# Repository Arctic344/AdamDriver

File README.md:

# AdamDriver, the PCA9685 based MotorDriver
I created a compact quad-motor driver for a project

It uses a PCA9685 PWM controller and two TB6612FNG chips to run up to 4 motors from 4.5V to 13.5V

It is functionally the same as [this arduino shield](https://learn.adafruit.com/adafruit-motor-shield-v2-for-arduino/overview), but without the servo drivers and such.

I dont know what I am doing, so please do not attempt to use this driver.

If for some reason you have a question about this stuff, add me @arctic344 on discord.

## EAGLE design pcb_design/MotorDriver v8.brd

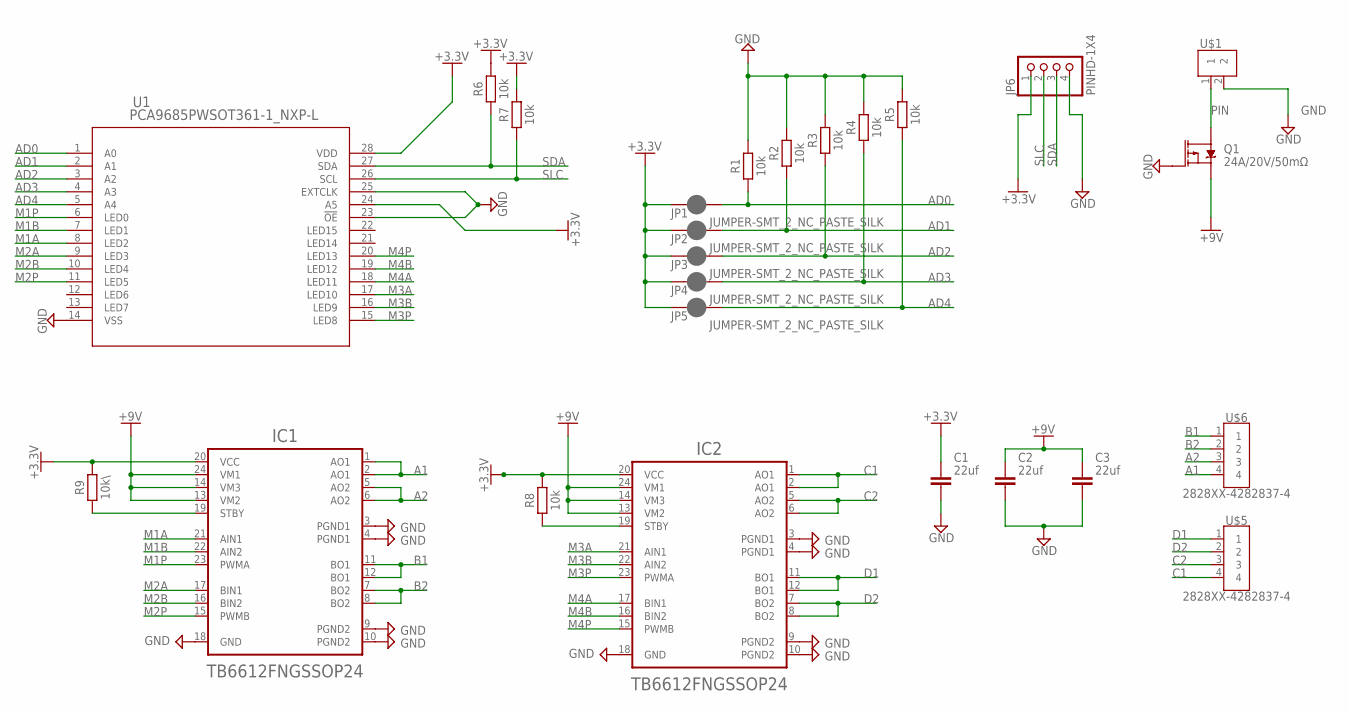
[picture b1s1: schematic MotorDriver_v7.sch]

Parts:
C1, C2, C3: 22uf; CAPC2012X110
IC1, IC2: TB6612FNGSSOP24; SOP65P760X160-24N
JP1, JP2, JP3, JP4, JP5: JUMPER-SMT_2_NC_PASTE_SILK; SMT-JUMPER_2_NC_PASTE_SILK
JP6: PINHD-1X4; 1X04
Q1: 24A/20V/50mΩ; TO220V
R1, R2, R3, R4, R5, R6, R7, R8: 10k; RESC1005X40
R9: 10k\; RESC1005X40
U1: PCA9685PWSOT361-1_NXP-L; SOT361-1_NXP-L
U$1: 2828XX-2282834-2; TERMBLK_254-2N
U$5, U$6: 2828XX-4282837-4; TERMBLK_508-4N

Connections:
+3.3V: C1.1, IC1.20 (VCC), IC2.20 (VCC), JP1.1, JP2.1, JP3.1, JP4.1, JP5.1, JP6.1, R6.2, R7.2, R8.2, R9.2, U1.24 (A5), U1.28 (VDD)
+9V: C2.1, C3.1, IC1.13 (VM2), IC1.14 (VM3), IC1.24 (VM1), IC2.13 (VM2), IC2.14 (VM3), IC2.24 (VM1), Q1.3 (S)
A1: IC1.1 (AO1), IC1.2 (AO1), U$6.4
A2: IC1.5 (AO2), IC1.6 (AO2), U$6.3
AD0: JP1.2, R1.1, U1.1 (A0)
AD1: JP2.2, R2.1, U1.2 (A1)
AD2: JP3.2, R3.1, U1.3 (A2)
AD3: JP4.2, R4.1, U1.4 (A3)
AD4: JP5.2, R5.1, U1.5 (A4)
B1: IC1.11 (BO1), IC1.12 (BO1), U$6.1
B2: IC1.7 (BO2), IC1.8 (BO2), U$6.2
C1: IC2.1 (AO1), IC2.2 (AO1), U$5.4
C2: IC2.5 (AO2), IC2.6 (AO2), U$5.3
D1: IC2.11 (BO1), IC2.12 (BO1), U$5.1
D2: IC2.7 (BO2), IC2.8 (BO2), U$5.2
GND: C1.2, C2.2, C3.2, IC1.3 (PGND1), IC1.4 (PGND1), IC1.9 (PGND2), IC1.10 (PGND2), IC1.18 (GND), IC2.3 (PGND1), IC2.4 (PGND1), IC2.9 (PGND2), IC2.10 (PGND2), IC2.18 (GND), JP6.4, Q1.1 (G), R1.2, R2.2, R3.2, R4.2, R5.2, U1.14 (VSS), U1.23 (!OE), U1.25 (EXTCLK), U$1.2
M1A: IC1.21 (AIN1), U1.8 (LED2)
M1B: IC1.22 (AIN2), U1.7 (LED1)
M1P: IC1.23 (PWMA), U1.6 (LED0)
M2A: IC1.17 (BIN1), U1.9 (LED3)
M2B: IC1.16 (BIN2), U1.10 (LED4)
M2P: IC1.15 (PWMB), U1.11 (LED5)
M3A: IC2.21 (AIN1), U1.17 (LED10)
M3B: IC2.22 (AIN2), U1.16 (LED9)
M3P: IC2.23 (PWMA), U1.15 (LED8)
M4A: IC2.17 (BIN1), U1.18 (LED11)
M4B: IC2.16 (BIN2), U1.19 (LED12)
M4P: IC2.15 (PWMB), U1.20 (LED13)
unnamed: IC2.19 (STBY), R8.1
unnamed: IC1.19 (STBY), R9.1
PIN: Q1.2 (D), U$1.1
SDA: JP6.3, R6.1, U1.27 (SDA)
SLC: JP6.2, R7.1, U1.26 (SCL)

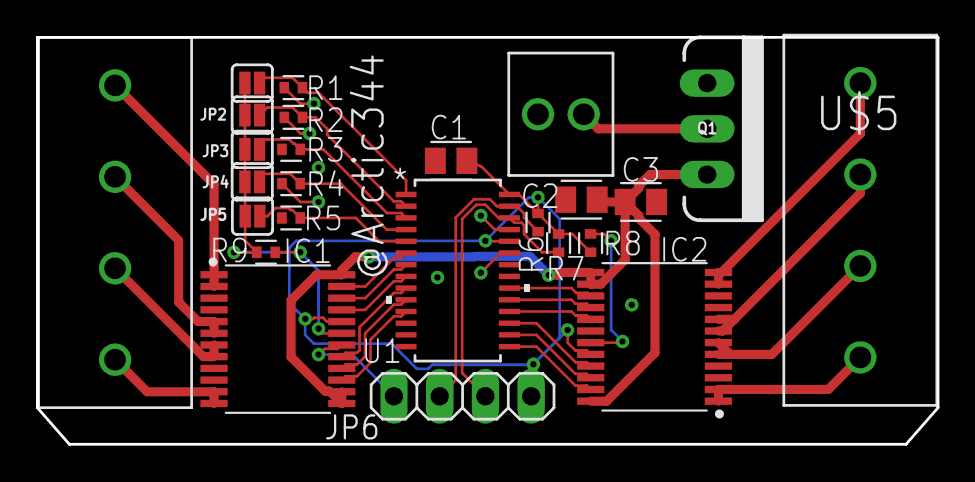
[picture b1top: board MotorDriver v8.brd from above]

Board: 2 copper layers, 50.0 x 22.6 mm, 25 parts (0 on the bottom side), 33 nets.

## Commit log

2023-10-20 I am testing how git works. Please igno
2023-10-20 Adding two files for the motor driver library
2023-10-20 Added some basic files to get me started
2023-10-20 Committing some basic files to get mestarted
2023-10-21 added new files
2023-10-24 Made the library
2023-10-24 test
2024-03-04 Chanfged name because i wanted to be funny.

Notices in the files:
parts and their libraries:
SparkFun-Jumpers: Licensing: Creative Commons ShareAlike 4.0 International - https://creativecommons.org/licenses/by-sa/4.0
COPYRIGHT: Copyright (C) 2023 Ultra Librarian. All rights reserved.
